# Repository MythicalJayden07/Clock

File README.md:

# 6-Digit 7-Segment Display Clock
This is a custom digital clock featuring a 6-digit 7-segment display packed into a clean, rectangular desktop case. I designed this to blend custom 3D-printed mechanics with a sleek, premium look by keeping the messy electronics hidden and using a real glass front panel.
## The Inspiration
I’ve always loved the raw, industrial look of 7-segment displays, but most DIY clocks you see online either look like a total rat's nest of bare wires or they’re stuck inside chunky 3D-printed plastic boxes that just feel a bit cheap.
I wanted to make something that actually looks like a premium desktop piece you'd buy at a store, while keeping that precise, retro-tech HH: MM :SS readout. The goal was to have a pristine glass front with zero visible screws or clunky printed bezels, but still have quick, toolless access to the PCB whenever I want to mess with the hardware.
## PCB Schematic
The brain of the clock. The schematic handles the multiplexing for the 6-digit display, power management, and the ATmega328P microcontroller layout to ensure clean signal lines without ghosting on the digits. 

## PCB Layout
A custom, compact board designed to slide perfectly into the case alignment channels. Component placement was adjusted so it sits perfectly behind the front glass face. 

## CAD Enclosure Design
The rectangular housing featuring the integrated top hinge and embedded slots for the neodymium magnets. This makes the door snap shut tight!!

## Bill of Materials (BOM)
[ClockBOM.csv](https://github.com/user-attachments/files/28500980/ClockBOM.csv)

| Reference | Qty | Value | Footprint / Details | Part Link |
| :--- | :---: | :--- | :--- | :--- |
| **U1** | 1 | ATmega328P-P | Package_DIP:DIP-28_W7.62mm Microcontroller | [Buy Link](https://www.mouser.in/ProductDetail/Microchip-Technology/ATMEGA328P-PU?qs=K8BHR703ZXguOQv3sKbWcg%3D%3D) |
| **U2 - U7** | 6 | TPIC6B595 | Package_DIP:DIP-20_W7.62mm Power Shift Register | [Buy Link](https://www.mouser.in/ProductDetail/Texas-Instruments/TPIC6B595N?qs=JHHQeKcAU3Cy7hDGJZD9fw%3D%3D) |
| **U8** | 1 | L7805 | Package_TO_SOT_THT:TO-220-3_Vertical Regulator | [Buy Link](https://www.mouser.in/ProductDetail/STMicroelectronics/L7805CV?qs=9NrABl3fj%2FqplZAHiYUxWg%3D%3D) |
| **DS1 - DS4** | 4 | SA18-11EWA | 1.8" Kingbright Red 7-Segment Display | [Buy Link](https://www.mouser.in/ProductDetail/Kingbright/SA18-11EWA?qs=JpELLRhtMc01ud%252BhiiNcbQ%3D%3D) |
| **DS5, DS6** | 2 | SA08-11GWA | 0.8" Kingbright Green 7-Segment Display | [Buy Link](https://www.mouser.in/ProductDetail/Kingbright/SA08-11GWA?qs=E09Sz5t5voVFPaAyTwzbvg%3D%3D) |
| **D1** | 1 | 1N5401 | Diode_THT:D_DO-201AD_Horizontal Rectifier | [Buy Link](https://www.mouser.in/ProductDetail/Diotec-Semiconductor/1N5401?qs=OlC7AqGiEDkgsZqkfh5%2F5g%3D%3D) |
| **Q1** | 1 | 2N3904 | Package_TO_SOT_THT:TO-92_Inline NPN Transistor | [Buy Link](https://www.mouser.in/ProductDetail/onsemi/2N3904BU?qs=or4AE2qAS%252Bd0Jdpn%2F8ktKg%3D%3D) |
| **F1** | 1 | 2A | Fuse:Fuse_Bourns_MF-RG300 Resettable PTC | [Buy Link](https://www.mouser.in/ProductDetail/Bourns/MF-RG300-0?qs=Zco4Fs67ctclSu06fHwNtw%3D%3D) |
| **Y1** | 1 | 16Mhz | Crystal:Crystal_HC49-U_Vertical Oscillator | [Buy Link](https://robu.in/product/hc49-s-16mhz-crystal-oscillator-pack-of-5/) |
| **C1** | 1 | 470uf | Capacitor_THT:CP_Radial_D8.0mm 25V Electrolytic | [Buy Link](https://robu.in/product/470uf-25v-electrolytic-capacitor-pack-of-3/) |
| **C3** | 1 | 100uf | Capacitor_THT:CP_Radial_D8.0mm 25V Electrolytic | [Buy Link](https://robu.in/?s=100uf+25v+radial+electrolyte+capacitor&post_type=product) |
| **C2, C4-C12, C15** | 11 | 100n | Capacitor_THT:C_Disc 0.1uF Ceramic Disc | [Buy Link](https://robu.in/?s=104+0.1uf+ceramic+disc+capacitor&post_type=product) |
| **C13, C14** | 2 | 22pf | Capacitor_THT:C_Disc 22pF Ceramic Disc | [Buy Link](https://robu.in/?s=22pf+ceramic+disc+capacitor&post_type=product) |
| **D2 - D5** | 4 | LED | LED_THT:LED_D5.0mm Red Status Indicator | [Buy Link](https://robu.in/?s=5mm+red+led+pack&post_type=product) |
| **R1-R7, R9-R15, R17-R23, R26-R32** | 28 | 390R | Resistor_THT:R_Axial 1/4W Carbon Film | (https://robu.in/?s=390+ohm+quarter+watt+resistor&post_type=product) |
| **R8, R16, R24, R33, R35-R50** | 20 | 620R | Resistor_THT:R_Axial 1/4W Carbon Film | (https://robu.in/?s=620+ohm+quarter+watt+resistor&post_type=product) |
| **R51, R55** | 2 | 1k | Resistor_THT:R_Axial 1/4W Carbon Film | (https://robu.in/?s=1k+ohm+quarter+watt+resistor&post_type=product) |
| **R52** | 1 | 270R | Resistor_THT:R_Axial 1/4W Carbon Film | (https://robu.in/?s=270+ohm+quarter+watt+resistor&post_type=product) |
| **R53, R54** | 2 | 10k | Resistor_THT:R_Axial 1/4W Carbon Film | (https://robu.in/?s=10k+ohm+quarter+watt+resistor&post_type=product) |
| **J1, J4** | 2 | Male Pins | 2.54mm Breakaway Vertical Headers | [Buy Link](https://www.digikey.in/en/products/detail/amphenol-cs-fci/68000-402HLF/1493940?s=N4IgTCBcDaIGwA4AMKC0AWJYASAZAYiALoC%2BQA and https://www.digikey.in/en/products/detail/amphenol-cs-fci/68000-406HLF/1878471?s=N4IgTCBcDaIGwA4AMKC0AWJcASAZAYiALoC%2BQA ) |
| **J2, J3** | 2 | Sockets | 2.54mm Vertical Female Pin Sockets | [Buy Link](https://www.digikey.in/en/products/detail/3m/929974-01-04-RK/1094257 and https://www.digikey.in/en/products/detail/3m/929974-01-06-RK/1094259) |
| **Case Hardware** | 6 | Magnets | N52 Neodymium Disc Magnets (3mm x 2mm) | [Buy Link](https://www.amazon.in/dp/B0BN8PHN9B) |
| **Case Hardware** | 1 | Glass Sheet | Custom cut clear front panel window (2mm) |  |

```

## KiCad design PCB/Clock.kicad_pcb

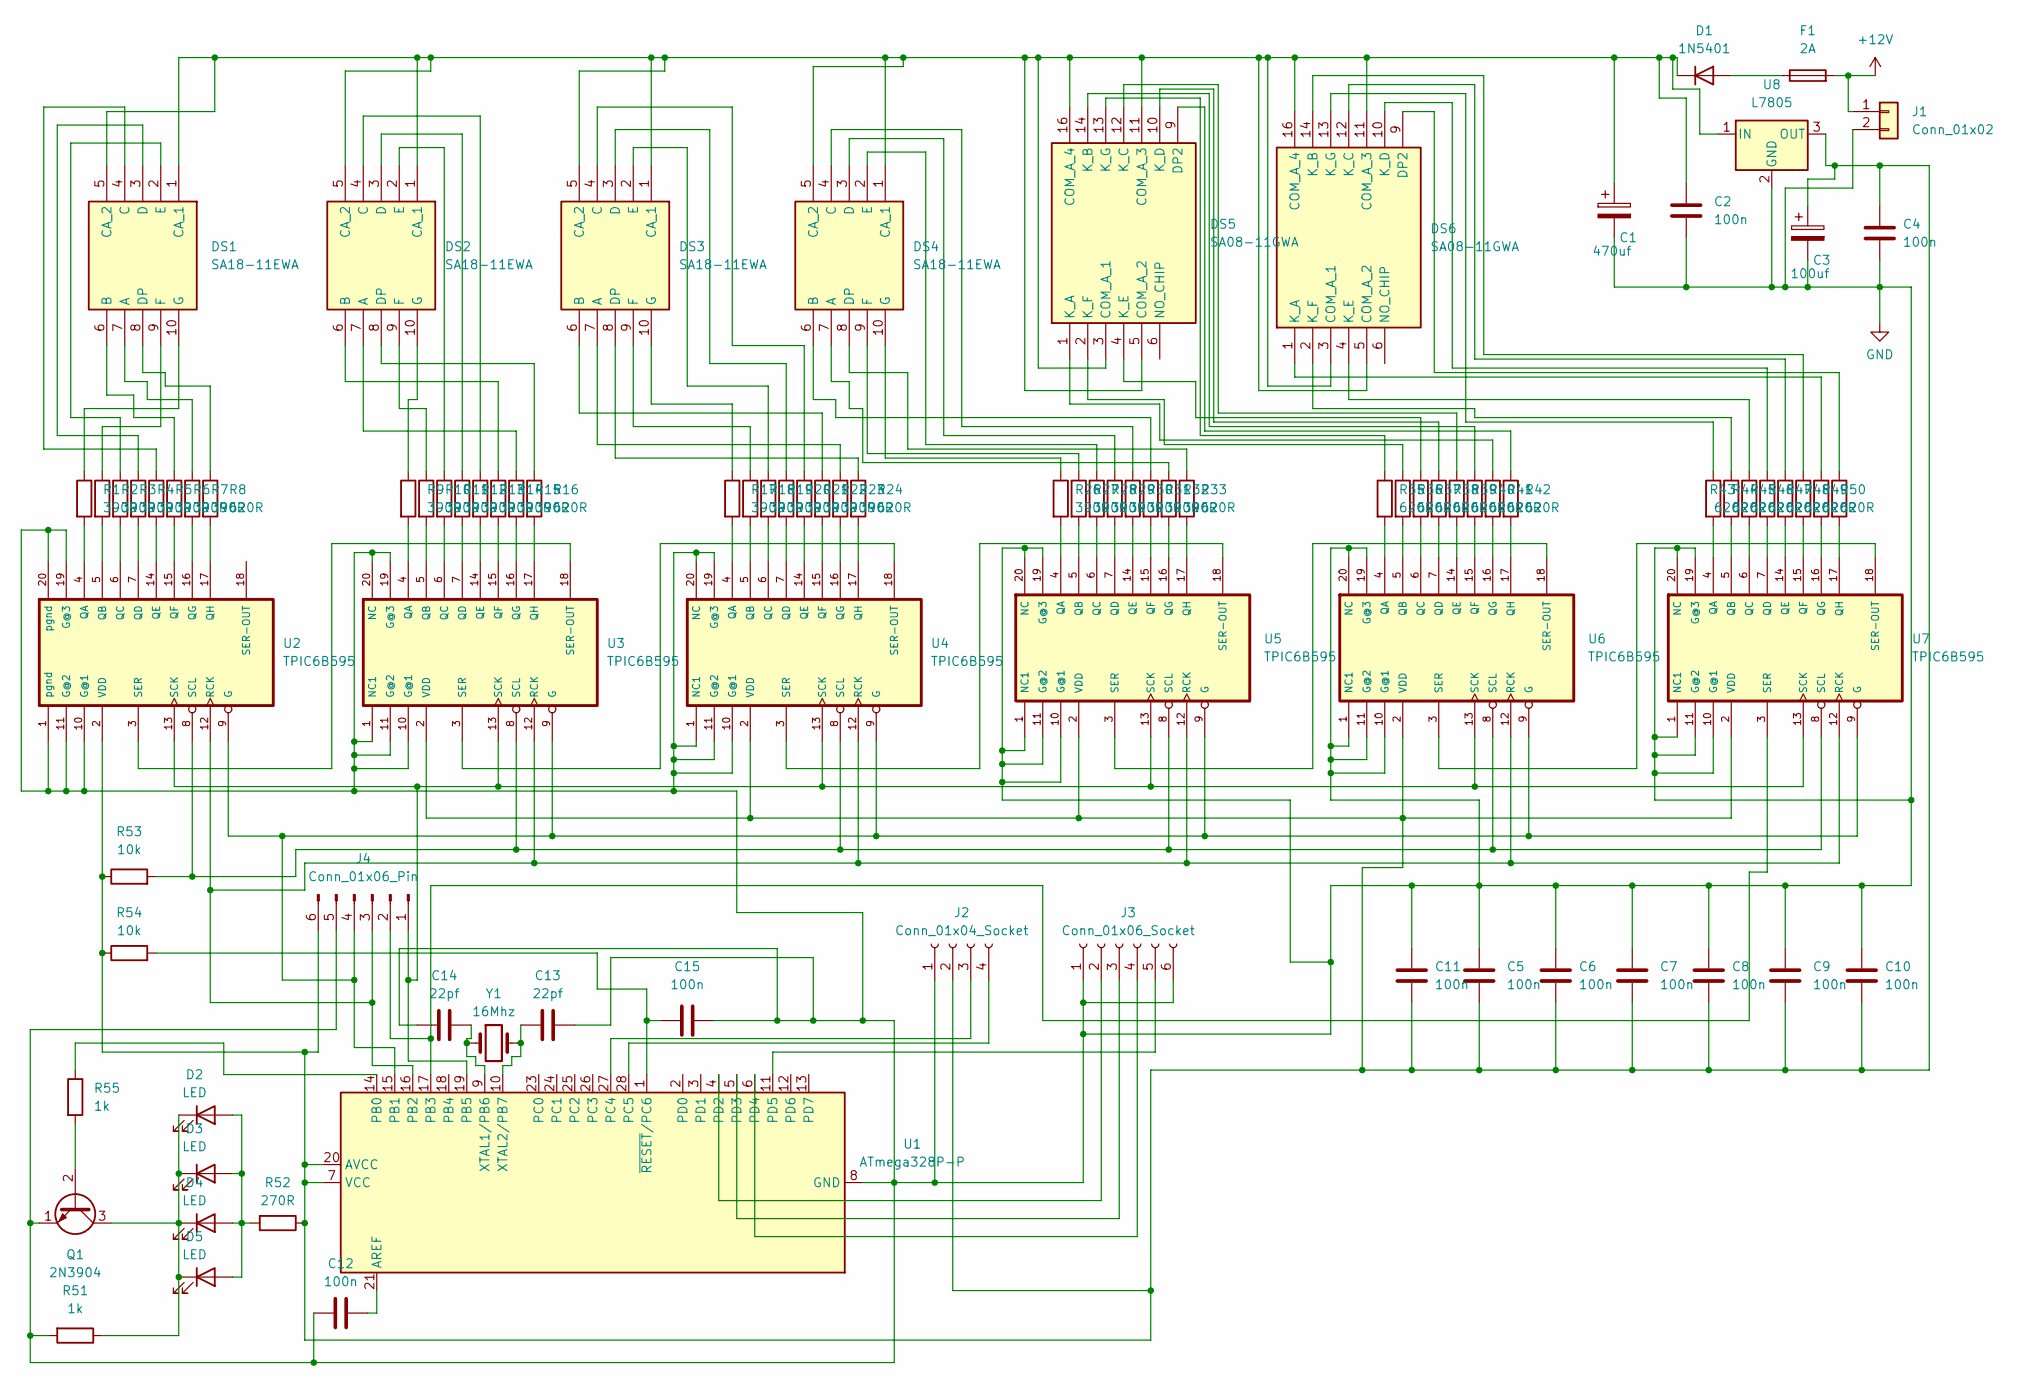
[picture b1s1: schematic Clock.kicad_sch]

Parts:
C1: 470uf; CP_Radial_D8.0mm_P3.50mm
C2, C4, C5, C6, C7, C8, C9, C10, C11, C12, C15: 100n; C_Disc_D5.0mm_W2.5mm_P5.00mm
C3: 100uf; CP_Radial_D8.0mm_P3.50mm
C13, C14: 22pf; C_Disc_D5.0mm_W2.5mm_P5.00mm
D1: 1N5401; D_DO-201AD_P15.24mm_Horizontal
D2, D3, D4, D5: LED; LED_D5.0mm
DS1, DS2, DS3, DS4: SA18-11EWA; My_Big_SA18_Display; Manufacturer_Part_Number SA18-11EWA; Mouser Part Number 604-SA18-11EWA
DS5, DS6: SA08-11GWA; My_Custom_SA08_Display; Manufacturer_Part_Number SA08-11GWA; Mouser Part Number 604-SA08-11GWA
F1: 2A; Fuse_Bourns_MF-RG300
J1: Conn_01x02; PinHeader_1x02_P2.54mm_Vertical
J2: Conn_01x04_Socket; PinSocket_1x04_P2.54mm_Vertical
J3: Conn_01x06_Socket; PinSocket_1x06_P2.54mm_Vertical
J4: Conn_01x06_Pin; PinHeader_1x06_P2.54mm_Vertical
Q1: 2N3904; TO-92_Inline
R1, R2, R3, R4, R5, R6, R7, R9, R10, R11, R12, R13, R14, R15, R17, R18, R19, R20, R21, R22, R23, R26, R27, R28, R29, R30, R31, R32: 390R; R_Axial_DIN0207_L6.3mm_D2.5mm_P10.16mm_Horizontal
R8, R16, R24, R33, R35, R36, R37, R38, R39, R40, R41, R42, R43, R44, R45, R46, R47, R48, R49, R50: 620R; R_Axial_DIN0207_L6.3mm_D2.5mm_P10.16mm_Horizontal
R51, R55: 1k; R_Axial_DIN0207_L6.3mm_D2.5mm_P10.16mm_Horizontal
R52: 270R; R_Axial_DIN0207_L6.3mm_D2.5mm_P10.16mm_Horizontal
R53, R54: 10k; R_Axial_DIN0207_L6.3mm_D2.5mm_P10.16mm_Horizontal
U1: ATmega328P-P; DIP-28_W7.62mm
U2, U3, U4, U5, U6, U7: TPIC6B595; DIP-20_W7.62mm
U8: L7805; TO-220-3_Vertical
Y1: 16Mhz; Crystal_HC49-U_Vertical

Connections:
+12V: F1.2, J1.1
GND: C1.2, C2.2, C3.2, C4.2, C5.1, C6.1, C7.1, C8.1, C9.1, C10.1, C11.1, C12.1, C13.2, C14.1, C15.2, J1.2, J2.1, J3.1, J3.6, J4.5, Q1.1 (E), R51.2, U1.8 (GND), U1.22 (GND), U2.1 (pgnd), U2.10 (G@1), U2.11 (G@2), U2.19 (G@3), U2.20 (pgnd), U3.1 (NC1), U3.10 (G@1), U3.11 (G@2), U3.19 (G@3), U3.20 (NC), U4.1 (NC1), U4.10 (G@1), U4.11 (G@2), U4.19 (G@3), U4.20 (NC), U5.1 (NC1), U5.10 (G@1), U5.11 (G@2), U5.19 (G@3), U5.20 (NC), U6.1 (NC1), U6.10 (G@1), U6.11 (G@2), U6.19 (G@3), U6.20 (NC), U7.1 (NC1), U7.10 (G@1), U7.11 (G@2), U7.19 (G@3), U7.20 (NC), U8.2 (GND)
unnamed: D1.2 (A), F1.1
unnamed: C1.1, C2.1, D1.1 (K), DS1.1 (CA_1), DS1.5 (CA_2), DS2.1 (CA_1), DS2.5 (CA_2), DS3.1 (CA_1), DS3.5 (CA_2), DS4.1 (CA_1), DS4.5 (CA_2), DS5.3 (COM_A_1), DS5.5 (COM_A_2), DS5.11 (COM_A_3), DS5.16 (COM_A_4), DS6.3 (COM_A_1), DS6.5 (COM_A_2), DS6.11 (COM_A_3), DS6.16 (COM_A_4), U8.1 (IN)
unnamed: D2.2 (A), D3.2 (A), D4.2 (A), D5.2 (A), R52.2
unnamed: D2.1 (K), D3.1 (K), D4.1 (K), D5.1 (K), Q1.3 (C), R51.1
unnamed: DS1.7 (A), R7.1
unnamed: DS1.6 (B), R6.1
unnamed: DS1.4 (C), R5.1
unnamed: DS1.3 (D), R4.1
unnamed: DS1.8 (DP), R8.1
unnamed: DS1.2 (E), R3.1
unnamed: DS1.9 (F), R2.1
unnamed: DS1.10 (G), R1.1
unnamed: DS2.7 (A), R15.1
unnamed: DS2.6 (B), R14.1
unnamed: DS2.4 (C), R13.1
unnamed: DS2.3 (D), R12.1
unnamed: DS2.8 (DP), R16.1
unnamed: DS2.2 (E), R11.1
unnamed: DS2.9 (F), R10.1
unnamed: DS2.10 (G), R9.1
unnamed: DS3.7 (A), R23.1
unnamed: DS3.6 (B), R22.1
unnamed: DS3.4 (C), R21.1
unnamed: DS3.3 (D), R20.1
unnamed: DS3.8 (DP), R24.1
unnamed: DS3.2 (E), R19.1
unnamed: DS3.9 (F), R18.1
unnamed: DS3.10 (G), R17.1
unnamed: DS4.7 (A), R32.1
unnamed: DS4.6 (B), R31.1
unnamed: DS4.4 (C), R30.1
unnamed: DS4.3 (D), R29.1
unnamed: DS4.8 (DP), R33.1
unnamed: DS4.2 (E), R28.1
unnamed: DS4.9 (F), R27.1
unnamed: DS4.10 (G), R26.1
unnamed: DS5.9 (DP2), R42.1
unnamed: DS5.1 (K_A), R41.1
unnamed: DS5.14 (K_B), R40.1
unnamed: DS5.12 (K_C), R39.1
unnamed: DS5.10 (K_D), R38.1
unnamed: DS5.4 (K_E), R37.1
unnamed: DS5.2 (K_F), R36.1
unnamed: DS5.13 (K_G), R35.1
unnamed: DS6.9 (DP2), R43.1
unnamed: DS6.1 (K_A), R50.1
unnamed: DS6.14 (K_B), R49.1
unnamed: DS6.12 (K_C), R48.1
unnamed: DS6.10 (K_D), R47.1
unnamed: DS6.4 (K_E), R46.1
unnamed: DS6.2 (K_F), R45.1
unnamed: DS6.13 (K_G), R44.1
unnamed: C3.1, C4.1, C5.2, C6.2, C7.2, C8.2, C9.2, C10.2, C11.2, J2.2, J4.6, R52.1, R53.1, R54.1, U1.7 (VCC), U1.20 (AVCC), U2.2 (VDD), U3.2 (VDD), U4.2 (VDD), U5.2 (VDD), U6.2 (VDD), U7.2 (VDD), U8.3 (OUT)
unnamed: J2.3, U1.27 (PC4)
unnamed: J2.4, U1.28 (PC5)
unnamed: J3.2, U1.4 (PD2)
unnamed: J3.3, U1.5 (PD3)
unnamed: J3.4, U1.6 (PD4)
unnamed: J3.5, U1.11 (PD5)
unnamed: J4.1, U1.19 (PB5), U2.13 (SCK), U3.13 (SCK), U4.13 (SCK), U5.13 (SCK), U6.13 (SCK), U7.13 (SCK)
unnamed: J4.2, U1.17 (PB3), U7.3 (SER)
unnamed: J4.3, U1.16 (PB2), U2.12 (RCK), U3.12 (RCK), U4.12 (RCK), U5.12 (RCK), U6.12 (RCK), U7.12 (RCK)
unnamed: J4.4, U1.15 (PB1), U2.9 (G), U3.9 (G), U4.9 (G), U5.9 (G), U6.9 (G), U7.9 (G)
unnamed: Q1.2 (B), R55.2
unnamed: C12.2, U1.21 (AREF)
unnamed: R55.1, U1.14 (PB0)
unnamed: C14.2, U1.9 (XTAL1/PB6), Y1.1
unnamed: C13.1, U1.10 (XTAL2/PB7), Y1.2
unnamed: C15.1, R54.2, U1.1 (~RESET/PC6)
unnamed: R1.2, U2.4 (QA)
unnamed: R2.2, U2.5 (QB)
unnamed: R3.2, U2.6 (QC)
unnamed: R4.2, U2.7 (QD)
unnamed: R5.2, U2.14 (QE)
unnamed: R6.2, U2.15 (QF)
unnamed: R7.2, U2.16 (QG)
unnamed: R8.2, U2.17 (QH)
unnamed: R53.2, U2.8 (SCL), U3.8 (SCL), U4.8 (SCL), U5.8 (SCL), U6.8 (SCL), U7.8 (SCL)
unnamed: U2.3 (SER), U3.18 (SER-OUT)
unnamed: R9.2, U3.4 (QA)
unnamed: R10.2, U3.5 (QB)
unnamed: R11.2, U3.6 (QC)
unnamed: R12.2, U3.7 (QD)
unnamed: R13.2, U3.14 (QE)
unnamed: R14.2, U3.15 (QF)
unnamed: R15.2, U3.16 (QG)
unnamed: R16.2, U3.17 (QH)
unnamed: U3.3 (SER), U4.18 (SER-OUT)
unnamed: R17.2, U4.4 (QA)
unnamed: R18.2, U4.5 (QB)
unnamed: R19.2, U4.6 (QC)
unnamed: R20.2, U4.7 (QD)
unnamed: R21.2, U4.14 (QE)
unnamed: R22.2, U4.15 (QF)
unnamed: R23.2, U4.16 (QG)
unnamed: R24.2, U4.17 (QH)
unnamed: U4.3 (SER), U5.18 (SER-OUT)
unnamed: R26.2, U5.4 (QA)
unnamed: R27.2, U5.5 (QB)
unnamed: R28.2, U5.6 (QC)
unnamed: R29.2, U5.7 (QD)
unnamed: R30.2, U5.14 (QE)
unnamed: R31.2, U5.15 (QF)
unnamed: R32.2, U5.16 (QG)
unnamed: R33.2, U5.17 (QH)
unnamed: U5.3 (SER), U6.18 (SER-OUT)
unnamed: R35.2, U6.4 (QA)
unnamed: R36.2, U6.5 (QB)
unnamed: R37.2, U6.6 (QC)
unnamed: R38.2, U6.7 (QD)
unnamed: R39.2, U6.14 (QE)
unnamed: R40.2, U6.15 (QF)
unnamed: R41.2, U6.16 (QG)
unnamed: R42.2, U6.17 (QH)
unnamed: U6.3 (SER), U7.18 (SER-OUT)
unnamed: R44.2, U7.4 (QA)
unnamed: R45.2, U7.5 (QB)
unnamed: R46.2, U7.6 (QC)
unnamed: R47.2, U7.7 (QD)
unnamed: R48.2, U7.14 (QE)
unnamed: R49.2, U7.15 (QF)
unnamed: R50.2, U7.16 (QG)
unnamed: R43.2, U7.17 (QH)

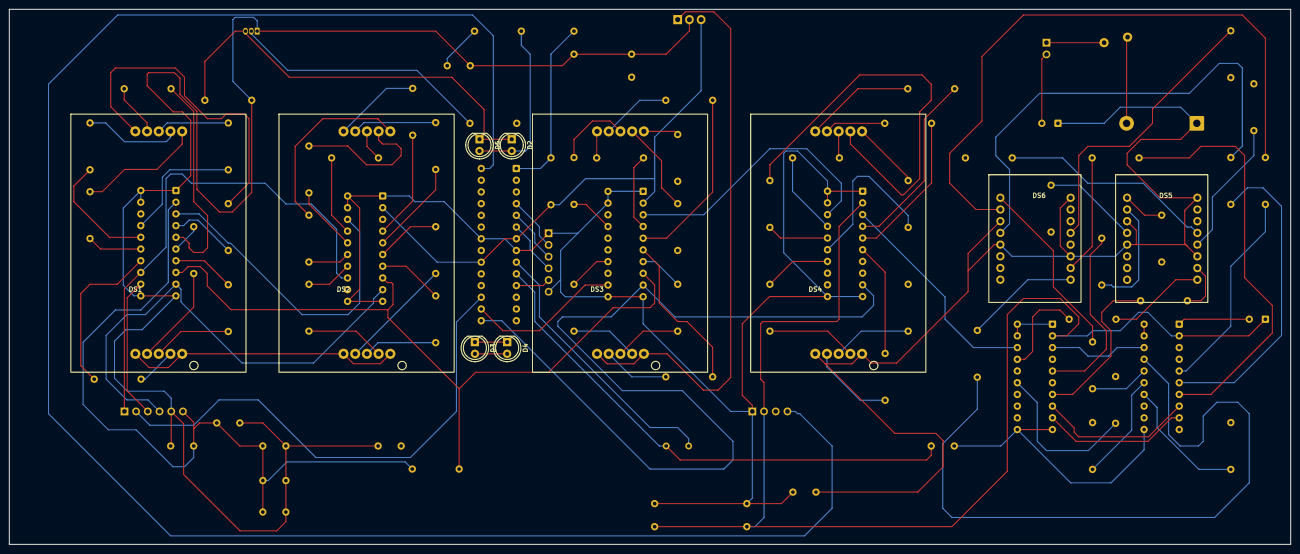
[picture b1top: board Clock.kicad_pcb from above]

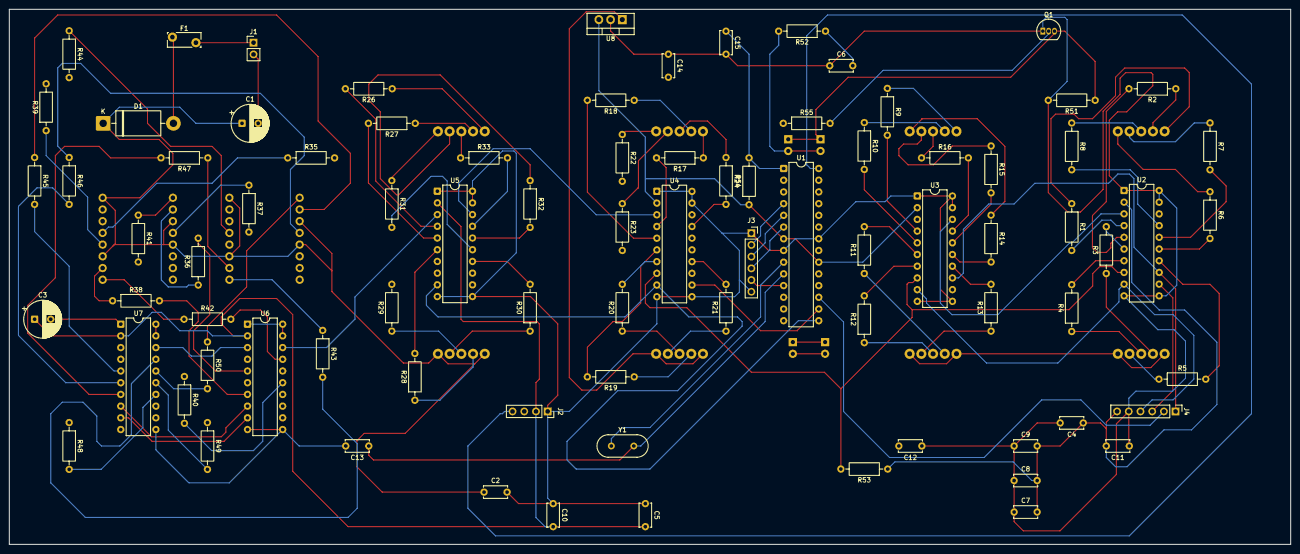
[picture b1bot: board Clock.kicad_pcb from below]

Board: 4 copper layers, 278.0 x 116.1 mm, 94 parts (84 on the bottom side), 125 nets.

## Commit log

2026-06-02 Enhance README with project details and BOM
    Expanded the README to include detailed project information, inspiration, PCB schematic, layout, CAD design, and a comprehensive Bill of Materials (BOM).
2026-06-02 Enhance README with BOM links and supplier information
    Updated the README to include a link to the BOM CSV file and added supplier links for components in the Bill of Materials section.
2026-06-02 Add Bill of Materials section to README
    Added a detailed Bill of Materials (BOM) section with components, quantities, values, footprints, and purchase links.
2026-06-02 Enhance README with Bill of Materials details
    Added detailed Bill of Materials (BOM) section with references, quantities, and links for components.
2026-06-02 Fix formatting in Bill of Materials section
2026-06-02 Update magnet quantity in hardware list
    Updated the quantity of N52 Neodymium Disc Magnets from 4 to 6 in the hardware list.
2026-06-02 Update component links in README.md
    Updated component links in the README to point to Digi-Key.
2026-06-13 Modify total estimated project hardware cost
    Updated total estimated project hardware cost.
2026-06-13 Refactor Bill of Materials section in README
    Removed duplicate Bill of Materials section and updated links for resistors.
2026-06-13 Create temp
2026-06-13 Create Firmware
